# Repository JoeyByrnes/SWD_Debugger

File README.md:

# SWD_Debugger
Design files for an SWD debugger based on the <a href="https://github.com/electronut/ElectronutLabs-Bumpy">bumpy probe</a>. Compatible with Black Magic Probe and ST-Link V2 firmware. 

Hardware Changes from Bumpy 2.0 Project:
- Changed male USB-A plug to a female USB-C receptacle
- Changed pinout of the SWD/UART pins so that all SWD related pins are on top and all UART & power pins are on bottom
- Changed form factor and created an enclosure out of a cover PCB and 3d printed spacers.
- Changed resonator to an equivalent option in a different package
- Changed STM32 to a different package of the same product (for sourcing purposes at the time of designing)
<br>
<br>

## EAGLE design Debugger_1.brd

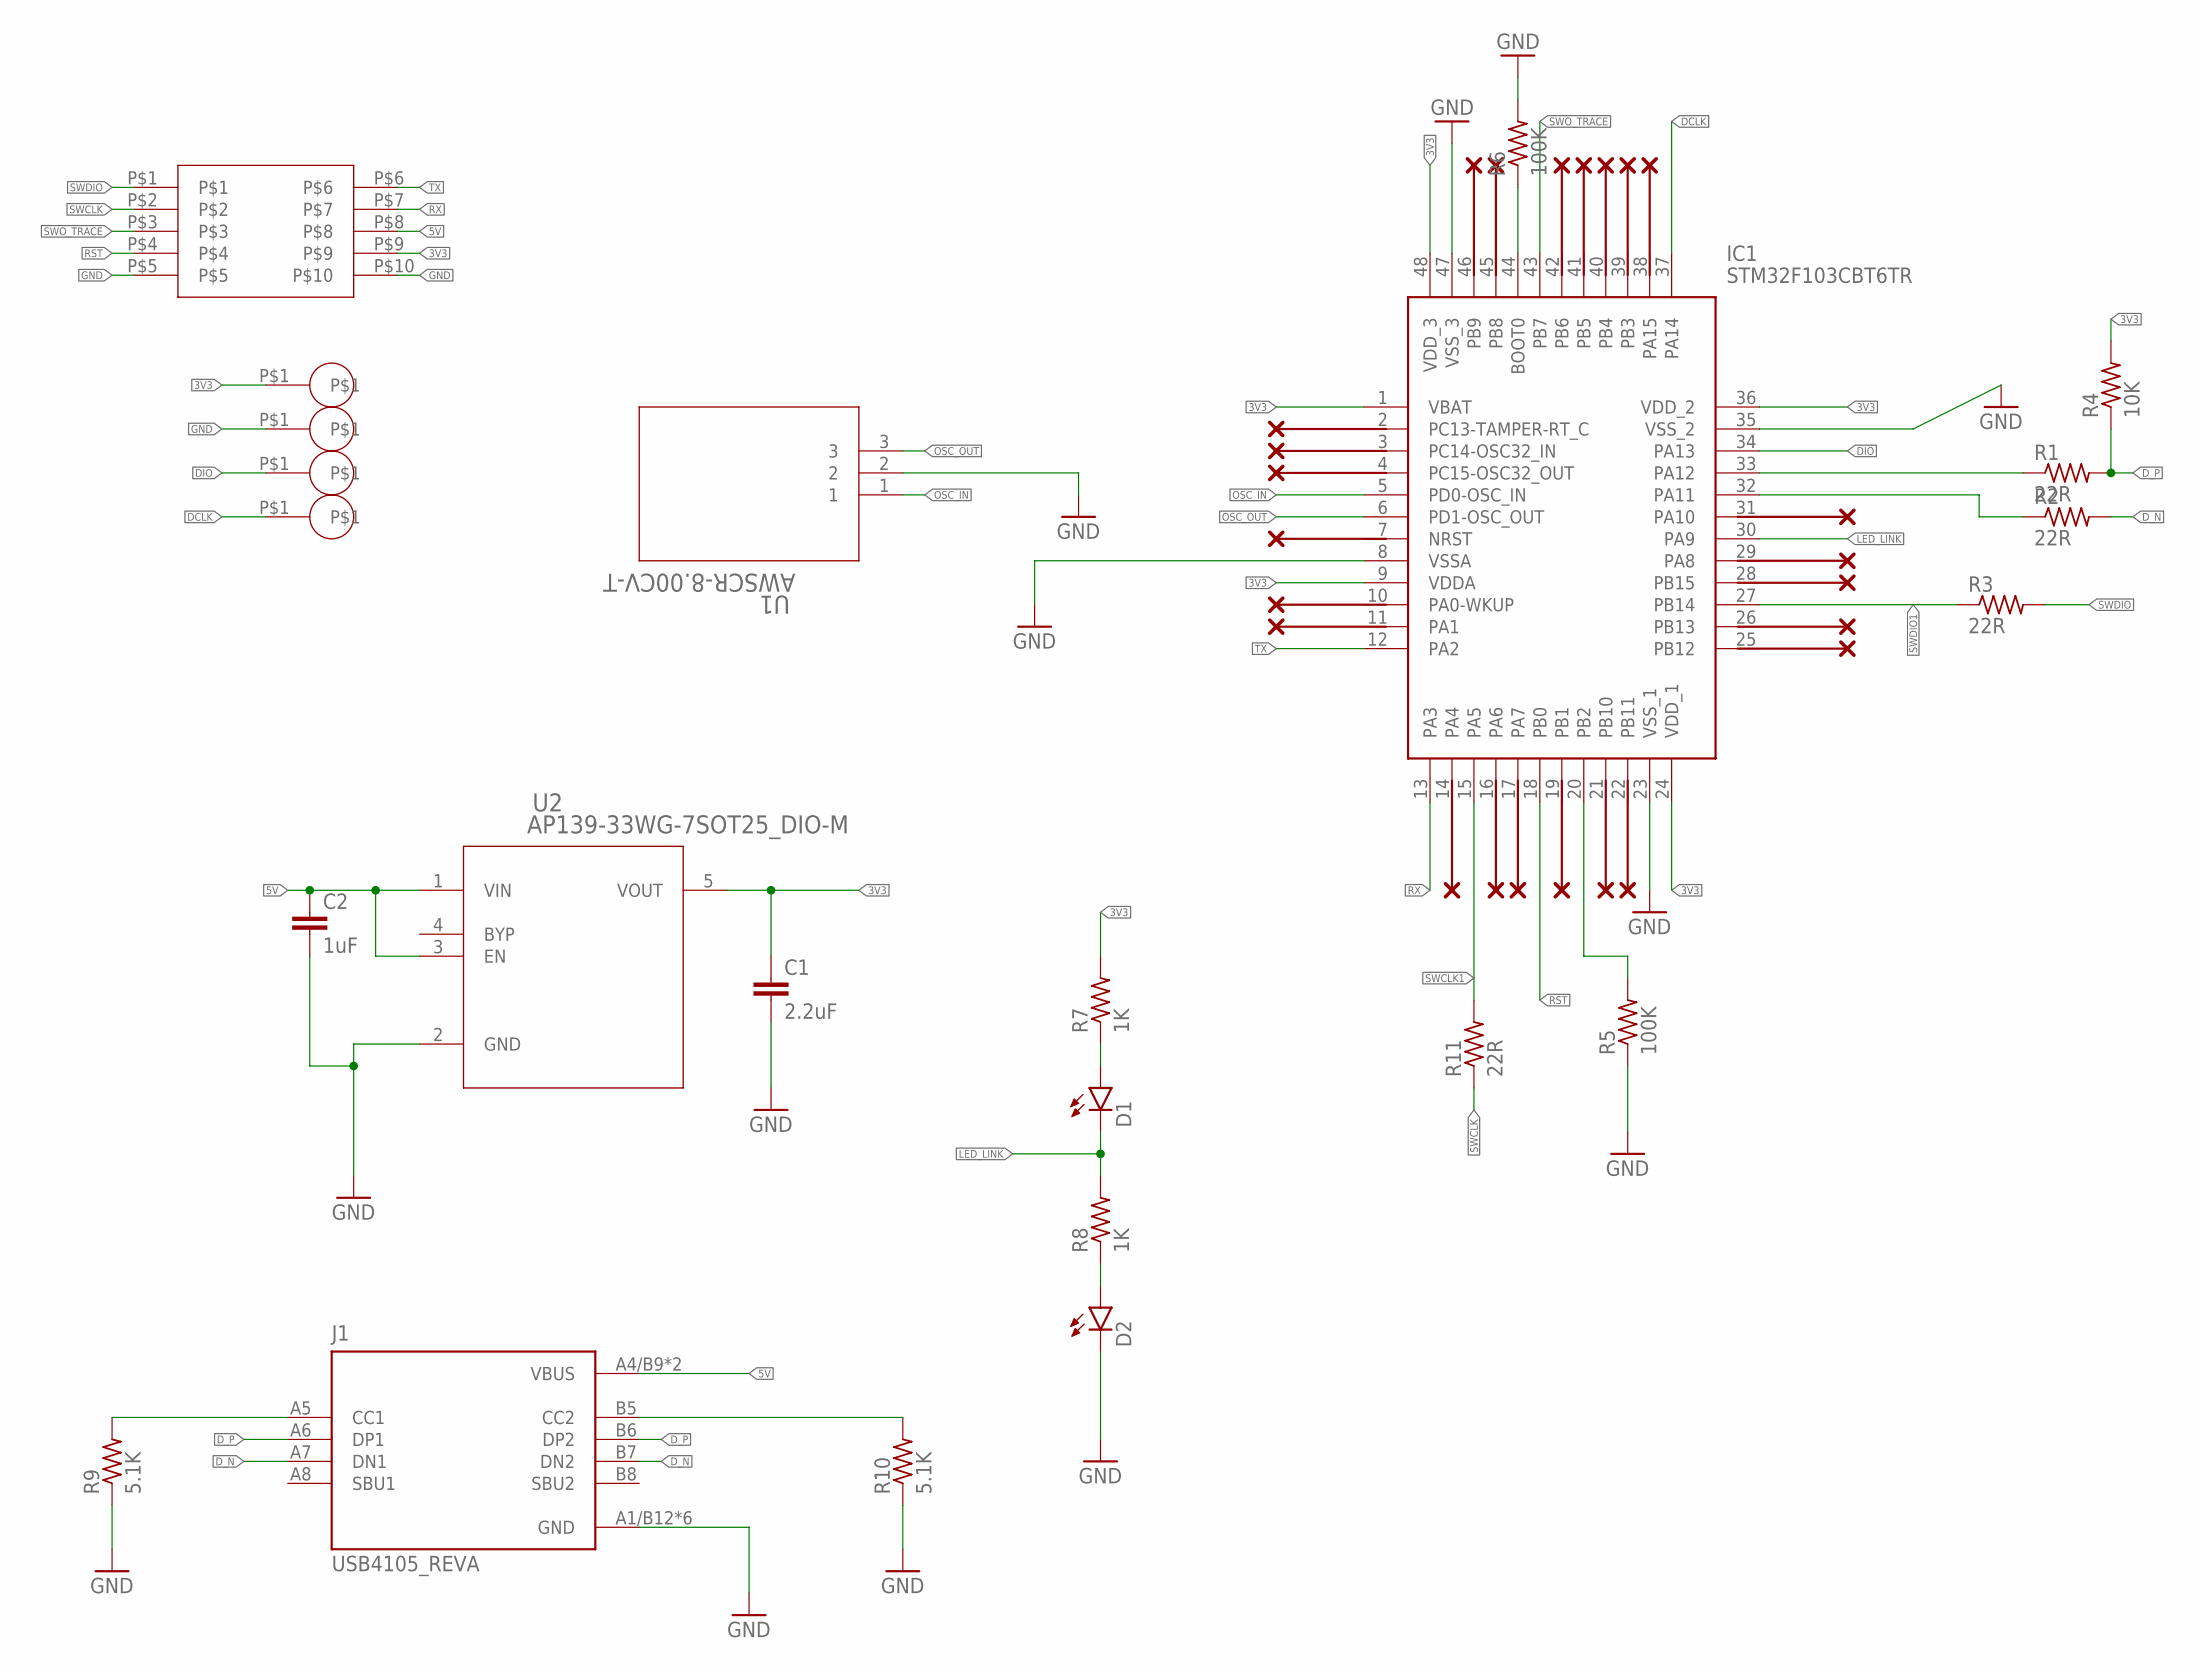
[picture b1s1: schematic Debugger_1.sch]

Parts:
C1: 2.2uF; C0603
C2: 1uF; C0603
D1, D2: LEDCHIPLED_0603; CHIPLED_0603
IC1: STM32F103CBT6TR; QFP50P900X900X160-48N
J1: USB4105_REVA; GCT_USB4105_REVA
R1, R2, R3, R11: 22R; R0603
R4: 10K; R0603
R5, R6: 100K; R0603
R7, R8: 1K; R0603
R9, R10: 5.1K; R0603
U1: AWSCR-8.00CV-T; AWSCR-8.00CV-T_ABR
U2: AP139-33WG-7SOT25_DIO-M; SOT25_DIO-M
U$25: SIDEWAYS_HEADER_10
U$26, U$27, U$28, U$29: SPRING_PAD_1

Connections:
3V3: C1.1, IC1.1 (VBAT), IC1.9 (VDDA), IC1.24 (VDD_1), IC1.36 (VDD_2), IC1.48 (VDD_3), R4.2, R7.2, U2.5 (VOUT), U$25.P$9, U$26.P$1
5V: C2.1, J1.A4/B9 (VBUS), J1.B4/A9 (VBUS), U2.1 (VIN), U2.3 (EN), U$25.P$8
DCLK: IC1.37 (PA14), U$29.P$1
DIO: IC1.34 (PA13), U$28.P$1
D_N: J1.A7 (DN1), J1.B7 (DN2), R2.2
D_P: J1.A6 (DP1), J1.B6 (DP2), R1.2, R4.1
GND: C1.2, C2.2, D2.C, IC1.8 (VSSA), IC1.23 (VSS_1), IC1.35 (VSS_2), IC1.47 (VSS_3), J1.A1/B12 (GND), J1.B1/A12 (GND), J1.G1 (GND), J1.G2 (GND), J1.G3 (GND), J1.G4 (GND), R5.1, R6.2, R9.1, R10.1, U1.2, U2.2 (GND), U$25.P$5, U$25.P$10, U$27.P$1
LED_LINK: D1.C, IC1.30 (PA9), R8.2
unnamed: IC1.20 (PB2), R5.2
unnamed: IC1.32 (PA11), R2.1
unnamed: IC1.33 (PA12), R1.1
unnamed: IC1.44 (BOOT0), R6.1
unnamed: D1.A, R7.1
unnamed: J1.A5 (CC1), R9.2
unnamed: D2.A, R8.1
unnamed: J1.B5 (CC2), R10.2
OSC_IN: IC1.5 (PD0-OSC_IN), U1.1
OSC_OUT: IC1.6 (PD1-OSC_OUT), U1.3
RST: IC1.18 (PB0), U$25.P$4
RX: IC1.13 (PA3), U$25.P$7
SWCLK: R11.1, U$25.P$2
SWCLK1: IC1.15 (PA5), R11.2
SWDIO: R3.2, U$25.P$1
SWDIO1: IC1.27 (PB14), R3.1
SWO_TRACE: IC1.43 (PB7), U$25.P$3
TX: IC1.12 (PA2), U$25.P$6

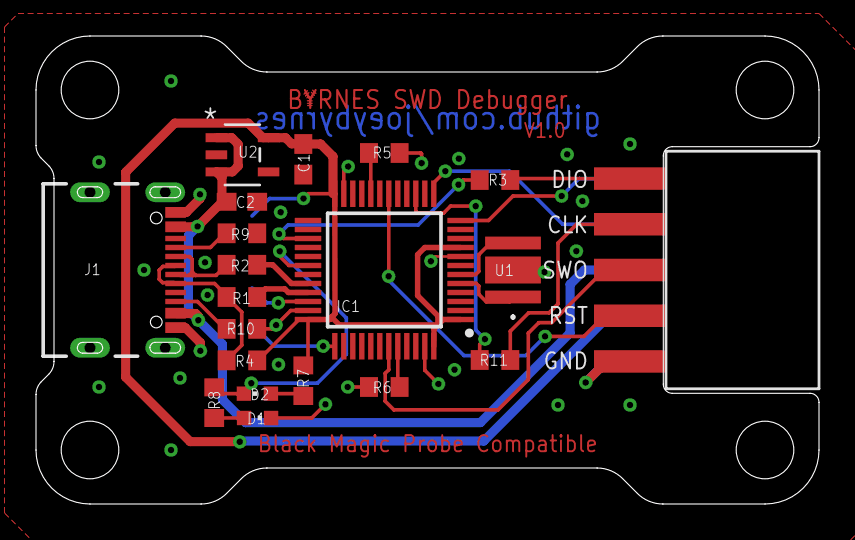
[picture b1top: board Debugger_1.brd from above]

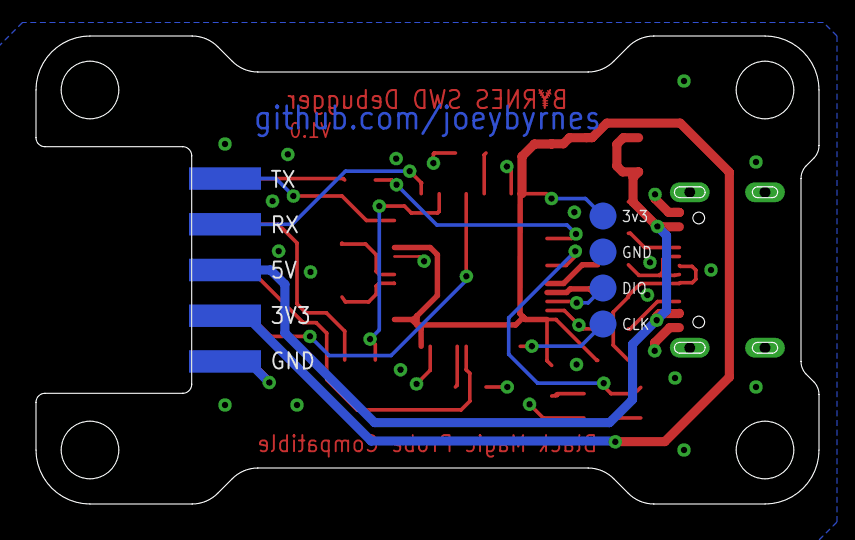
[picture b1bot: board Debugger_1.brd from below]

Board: 2 copper layers, 43.5 x 26.0 mm, 24 parts (4 on the bottom side), 26 nets.

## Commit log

2023-10-07 Created README.md
2023-10-07 added source and gerber files
2023-10-08 Added enclosure 3d print files

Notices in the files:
parts and their libraries:
COPYRIGHT: Copyright (C) 2021 Ultra Librarian. All rights reserved.
